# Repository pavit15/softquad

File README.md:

Soft Quad
===
## Table of Contents
- [About The Project](#about_the_project)
    - [Key elements of the project](#key_elements_of_the_project)
    - [Tech Stack](#tech_stack)
- [Getting Started](#getting_started)
    - [Prerequisites](#prerequisites)
    - [Installations](#installations)
- [Theory and Approach](#theory_and_approach) 
    - [Design of robot chassis](#design_of_robot_chasis)
    - [Selecting Flex Material for the bot](#selecting_material_for_the_bot)
- [Troit Gait Algorithm](#troit_gait_algorithm)
- [Challenges faced and solutions applied](#challenges_faced_and_solutions_applied)
- [Contributors](#contributors)
- [Acknowledgement and Resources](#acknowledgement_and_resources)
---

# <ins>About the Project
**To create a robot capable of overcoming obstacle using soft materials.**
Basically, in our project, we use flex material instead of rigid materials such as PLA. We used Ecoflex Dragon skin material for the body. A Flex PCB will enable our SoftQuad robot to become more flexible, improving its capacity to scale higher obstacles.
  
## <ins>Key elements of the project:
### 1. Mechanical design
The mechanical design and fabrication aspect of the project involve creating a design which is durable, flexible and lightweight to enable efficient movement. This design ensures both agility and robustness, allowing the robot to traverse challenging terrains while maintaining stability and precision.

### 2. Embedded design
In the core of the system, we use ESP32, a powerful microcontroller with built-in Wi-Fi and Bluetooth capabilities. It is programmed using the ESP-IDF (IoT Development Framework), which provides the tools and libraries necessary to develop applications for the microcontroller.

### 3. PCB design
The PCB (Printed Circuit Board) design involves creating a custom circuit board that has various electronic components such as microcontrollers, motor drivers, sensors, communication modules, and power management units. 

We used a Flex PCB, which is a type of electronic circuit board that is made from flexible and bendable materials instead of rigid materials like in traditional PCB’s. They offer a range of benefits due to their flexibility, allowing them to be shaped, folded, or bent to fit into various form factors and spaces that rigid PCBs cannot accommodate.
### 4. Soft robotics
Unlike traditional rigid robots, this project utilizes soft robotics principles to create a robot with a pliable and deformable structure. This inherent flexibility allows the robot to adapt its shape to various obstacles, enhancing its ability to traverse complex terrains.</ins>
</ins>

## <ins>Tech Stack
- Embedded C
- SolidWorks
- KiCAD
- Altium
- ESP-IDF
- Ultimaker Cura
    
# <ins>Getting Started
## <ins>Prerequisites
1. Used [ESP-IDFv4.4](https://docs.espressif.com/projects/esp-idf/en/latest/esp32/get-started) for building and flashing the controller code.
2. Used [KiCad](https://www.kicad.org/) For designing the rigid PCB
3. Used [Altium](https://www.altium.com/) For designing the flex PCB   
4. Used [Solidworks](https://www.solidworks.com/) for designing the bot and mold for soft bot.
5. Used [Ultimaker Cura](https://ultimaker.com/software/ultimaker-cura/) for 3D printing the parts

## <ins>Installations
1. Installing ESP-IDF:
[For Windows](https://docs.espressif.com/projects/esp-idf/en/latest/esp32/get-started/windows-setup.html)
[For Linux or MacOS](https://docs.espressif.com/projects/esp-idf/en/latest/esp32/get-started/linux-macos-setup.html)

# <ins>Theory and Approach
### Design of robot chasis
- We designed the chasis of the bot on Solidworks.

### Selecting Flex Material for the bot
- For the bot material, we had to choose between Dragon Skin, Eco-Flex 00-30, Eco-Flex 00-50
- After taking into account factors such as flexibility, durability, elasticity and stability, we concluded that Dragon Skin is the material most comparable to PDMS in terms of its flexibility, translucency, and biocompatibility. It is often used as a substitute when PDMS like properties are required, making it a versatile and obvious choice for applications such as soft robotics. 

## <ins>Trot Gait Algorithm
We controlled the movement of the bot through our ESP-32 controller. The motion that the bot follows is that of the horse trot gait. 
Here is a flowchart explaining the code: 

## <ins>PCB Design on KiCAD
Fornt side of PCB

Backside

## <ins>Challenges faced and solutions applied  
At first, the weight of the body was bending the flex legs since they were unable to support the weight of the bot. In order to allow the legs to move, we altered the leg's measurements and added thickness.Managing the soft robotics part is taking some time.
The main hardware and circuit problem we encountered was voltage control, or the inability to supply the appropriate and sufficient voltage to the corresponding electrical equipment.
We had to move to Altium because Kicad would not allow us to define stack layers, or create a flexible PCB with stiffeners. It took some getting used to.

## <ins>Making the flex body
For testing purposes, we made the rigid body of the bot using 3D printing first. After finishing with testing, we made the molds for the bot and 3D printed them. Then we made the mold of the bot using Dragon Skin material. For this process, initially we mixed the material  in 1:1 ratio for around 1 minute. Then we put this mixture in the mold and left it for around 2 hours.
    
DragonSkin material in the mold:

## <ins>Contributors
[Atharva Atre](https://github.com/AtharvaAtre)
[Pavit Kaur](https://github.com/pavit15)
[Varad Naik](https://github.com/VaradNaik921)
    
---

## <ins>Acknowledgement and Resources
Thanks to Our Mentors [Chinmay Mundane](https://github.com/ChinmayMundane), [Vaidic Gupta](https://github.com/Vaidicgupta) for Mentoring and Guiding us in our project.

Special Thanks to [SRA VJTI](https://sravjti.in/) for giving us the opportunity to do the project.

**Resources:**
- [**SoftBot Research Paper**](https://repository.bilkent.edu.tr/server/api/core/bitstreams/3dedb9bb-7897-4cc8-92b2-c85b78272922/content)
- [**ESP-IDF Resources**](https://docs.espressif.com/projects/esp-idf/en/latest/esp32/get-started/)
- [**KiCad Playlist**](https://www.youtube.com/playlist?list=PLn6004q9oeqGl91KifK6xHGuqvXGb374G)
- [**Solidworks Playlist**](https://www.youtube.com/playlist?list=PLrOFa8sDv6jcp8E3ayUFZ4iNI8uuPjXHe)

---

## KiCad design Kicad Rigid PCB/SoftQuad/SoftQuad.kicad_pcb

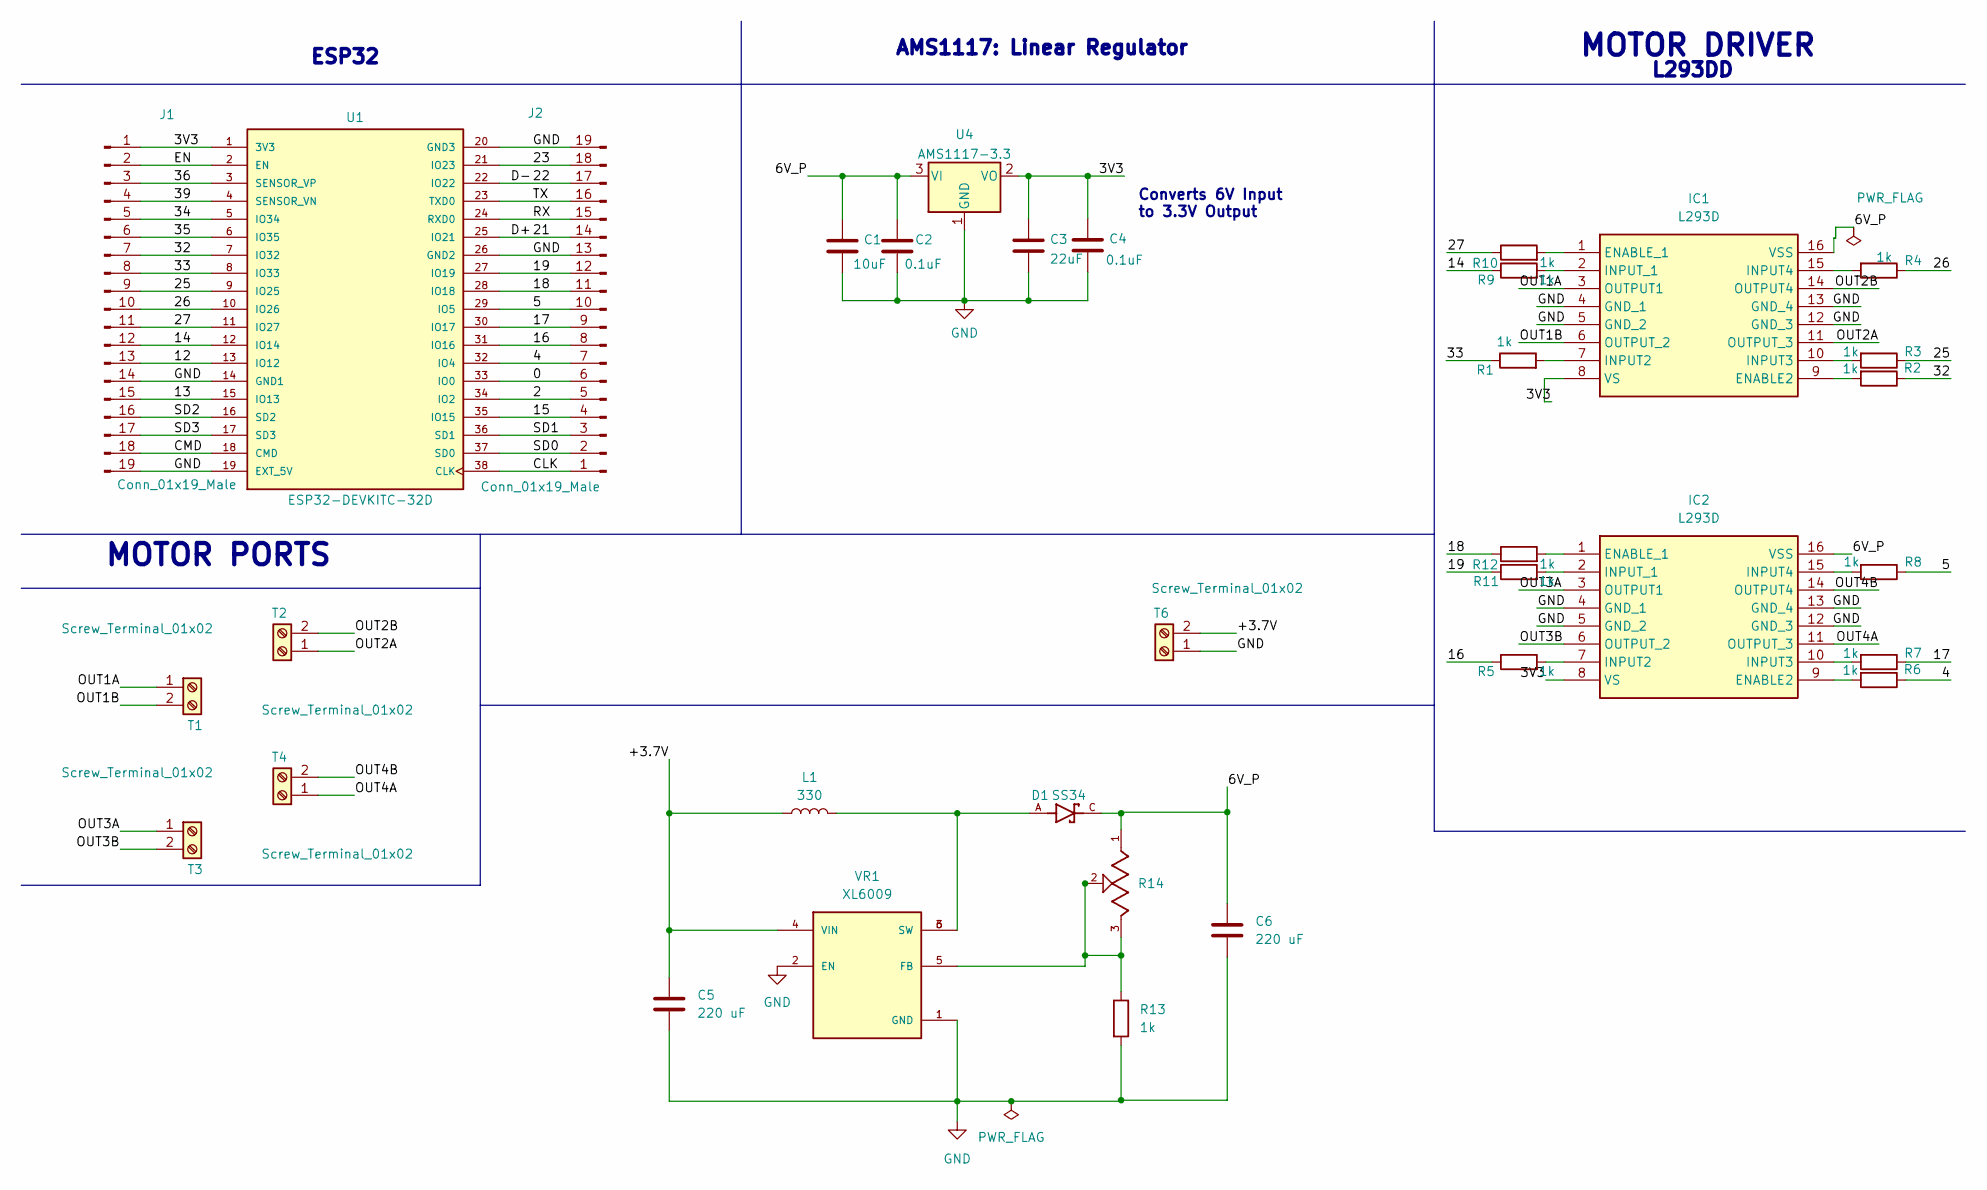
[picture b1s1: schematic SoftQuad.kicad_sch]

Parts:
C1: 10uF; C_0603_1608Metric
C2, C4: 0.1uF; C_0603_1608Metric
C3: 22uF; C_0603_1608Metric
C5, C6: 220 uF; C_0201_0603Metric
D1: SS34; DIOM7959X265N; PARTREV 31 Aug 2016
IC1, IC2: L293D; DIP880W50P254L2000H510Q16N; Manufacturer_Part_Number L293D; Mouser Part Number 511-L293D
J1, J2: Conn_01x19_Male; 1X19
L1: 330; L_0201_0603Metric
R1, R2, R3, R4, R5, R6, R7, R8, R9, R10, R11, R12, R13: 1k; R_0201_0603Metric
R14: 10k; TRIM_3352T-1-504LF; PARTREV 08/19
T1, T2, T3, T4, T6: Screw_Terminal_01x02; TerminalBlock_bornier-2_P5.08mm
U1: ESP32-DEVKITC-32D; ESP32-DEVKITCv4-32D; PARTREV 4
U4: AMS1117-3.3; SOT-223-3_TabPin2
VR1: XL6009; DPAK170P1435X465-6N; PARTREV 1.1

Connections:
/0: J2.6, U1.33 (IO0)
/2: J2.5, U1.34 (IO2)
/3V3: C3.1, C4.1, IC1.8 (VS), IC2.8 (VS), U1.1 (3V3), U4.2 (VO)
/4: R6.1, U1.32 (IO4)
/5: R8.1, U1.29 (IO5)
/6V_P: C1.1, C2.1, C6.1, D1.C, IC1.16 (VSS), IC2.16 (VSS), R14.1, U4.3 (VI)
/12: J1.13, U1.13 (IO12)
/13: J1.15, U1.15 (IO13)
/14: R9.1, U1.12 (IO14)
/15: J2.4, U1.35 (IO15)
/16: R5.1, U1.31 (IO16)
/17: R7.1, U1.30 (IO17)
/18: J2.11, R12.1, U1.28 (IO18)
/19: J2.12, R11.1, U1.27 (IO19)
/21: J2.14, U1.25 (IO21)
/22: J2.17, U1.22 (IO22)
/23: J2.18, U1.21 (IO23)
/25: R3.1, U1.9 (IO25)
/26: R4.1, U1.10 (IO26)
/27: R10.1, U1.11 (IO27)
/32: R2.1, U1.7 (IO32)
/33: R1.1, U1.8 (IO33)
/34: J1.5, U1.5 (IO34)
/35: J1.6, U1.6 (IO35)
/36: J1.3, U1.3 (SENSOR_VP)
/39: J1.4, U1.4 (SENSOR_VN)
/+3.7V: C5.1, L1.1, T6.2, VR1.4 (VIN)
/CLK: J2.1, U1.38 (CLK)
/CMD: J1.18, U1.18 (CMD)
/EN: J1.2, U1.2 (EN)
/OUT1A: IC1.3 (OUTPUT1), T1.1
/OUT1B: IC1.6 (OUTPUT_2), T1.2
/OUT2A: IC1.11 (OUTPUT_3), T2.1
/OUT2B: IC1.14 (OUTPUT4), T2.2
/OUT3A: IC2.3 (OUTPUT1), T3.1
/OUT3B: IC2.6 (OUTPUT_2), T3.2
/OUT4A: IC2.11 (OUTPUT_3), T4.1
/OUT4B: IC2.14 (OUTPUT4), T4.2
/RX: J2.15, U1.24 (RXD0)
/SD0: J2.2, U1.37 (SD0)
/SD1: J2.3, U1.36 (SD1)
/SD2: J1.16, U1.16 (SD2)
/SD3: J1.17, U1.17 (SD3)
/TX: J2.16, U1.23 (TXD0)
GND: C1.2, C2.2, C3.2, C4.2, C5.2, C6.2, IC1.4 (GND_1), IC1.5 (GND_2), IC1.12 (GND_3), IC1.13 (GND_4), IC2.4 (GND_1), IC2.5 (GND_2), IC2.12 (GND_3), IC2.13 (GND_4), R13.2, T6.1, U1.14 (GND1), U1.19 (EXT_5V), U1.20 (GND3), U1.26 (GND2), U4.1 (GND), VR1.1 (GND), VR1.2 (EN)
unnamed: D1.A, L1.2, VR1.3 (SW), VR1.6 (SW)
unnamed: IC1.9 (ENABLE2), R2.2
unnamed: IC1.1 (ENABLE_1), R10.2
unnamed: IC1.7 (INPUT2), R1.2
unnamed: IC1.10 (INPUT3), R3.2
unnamed: IC1.15 (INPUT4), R4.2
unnamed: IC1.2 (INPUT_1), R9.2
unnamed: IC2.9 (ENABLE2), R6.2
unnamed: IC2.1 (ENABLE_1), R12.2
unnamed: IC2.7 (INPUT2), R5.2
unnamed: IC2.10 (INPUT3), R7.2
unnamed: IC2.15 (INPUT4), R8.2
unnamed: IC2.2 (INPUT_1), R11.2
unnamed: R13.1, R14.2, R14.3, VR1.5 (FB)

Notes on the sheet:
L293DD
Converts 6V Input to 3.3V Output
MOTOR DRIVER
MOTOR PORTS
ESP32
AMS1117: Linear Regulator

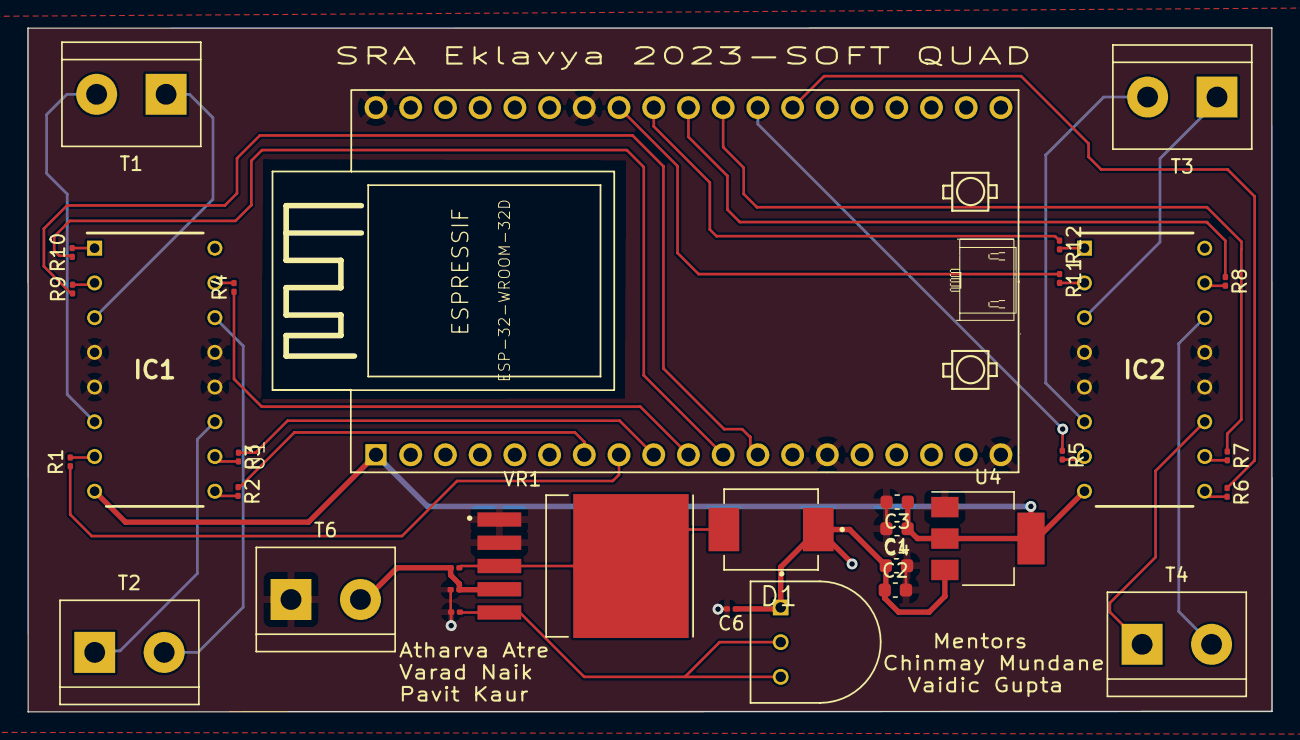
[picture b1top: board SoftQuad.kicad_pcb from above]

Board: 2 copper layers, 91.0 x 50.0 mm, 32 parts (0 on the bottom side), 38 nets.

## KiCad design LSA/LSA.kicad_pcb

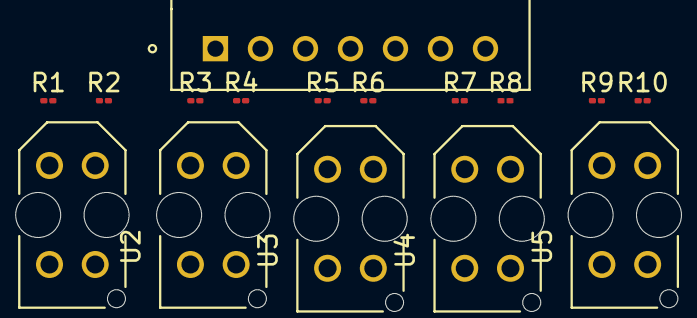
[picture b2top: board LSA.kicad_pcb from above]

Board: 2 copper layers, 16 parts (0 on the bottom side), 12 nets, no tracks yet.

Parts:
P1: S7B-XH-A(LF)(SN); JST_S7B-XH-A(LF)(SN)
R1, R3, R5, R7, R9: 4.7K; R_01005_0402Metric
R2, R4, R6, R8, R10: 150R; R_01005_0402Metric
U1, U2, U3, U4, U5: TCRT5000; OPTO_TCRT5000

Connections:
/3V3: P1.7, R1.1, R2.2, R3.1, R4.2, R5.1, R6.2, R7.1, R8.2, R9.1, R10.2
/A0-36: P1.1, R1.2, U1.COLL
/A1-39: P1.2, R3.2, U2.COLL
/A2-34: P1.3, R5.2, U3.COLL
/A3-35: P1.4, R7.2, U4.COLL
/A4-32: P1.5, R9.2, U5.COLL
/GND: P1.6, U1.CATH, U1.E, U2.CATH, U2.E, U3.CATH, U3.E, U4.CATH, U4.E, U5.CATH, U5.E
unnamed: R2.1, U1.A
unnamed: R4.1, U2.A
unnamed: R6.1, U3.A
unnamed: R8.1, U4.A
unnamed: R10.1, U5.A

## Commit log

2023-08-18 Create ESP 32 Pins, Normal and parallel mode in ESP32
2023-08-18 Create Code LED Flash and Hello World
2023-08-19 last changed at Aug 19, 2023 11:40 PM, pushed by pavit
2023-08-19 ESP-IDF Flash Commands
2023-08-19 README.md
2023-08-20 ESP IDF Commands.md
2023-08-20 LED Blink.md
2023-08-24 SoftQuad.md
2023-08-24 Create a
2023-08-24 ESP32.md
2023-08-24 PWM.md
2023-09-23 Create Solidwork Parts
2023-11-04 Create aa
2023-11-04 Components used for solidworks assembly
2023-11-04 Solidworks Rigid Bot Parts
2023-11-04 Rigid Bot Designs
    Final Design used for 3D printing and making of Rigid Bot
2023-11-04 Mold Designs
    Molds used for Making the flexible parts
2023-11-04 Molds Solidworks
    Mold Designs used for making flexible chassis and legs
2023-11-04 STL Files for 3D Printing
    STL files used for 3D printing the mold and parts of rigid bot
2023-11-04 STL Files used in 3D printing
    STL files used for 3D printing the parts of rigid bot and mold used in making soft bot
2023-11-04 Prototype cad model
2023-11-04 Prototype CAD Models
2023-11-04 assets for cad_design
2023-11-04 Assembly Files
    Assembly created for bot
2023-11-04 Adding Report
2023-11-05 assets
2023-11-05 Prototype PCB design for 6V battery
2023-11-05 Final Flex PCB design for a 3.7V Battery
2023-11-05 LSA PCB Design(Practice)
2023-11-05 components used in assembly
2023-11-05 Models of Rigid Bot
2023-11-05 Rigid Bot Models
2023-11-05 Molds for Soft Bot Fabrication
2023-11-05 STL Files used for 3D printing
2023-11-05 STL Files for 3D Printing
2023-11-05 Assembly of Bot in Solidworks
2023-11-05 Assembly of Bot
2023-11-05 Rigid PCB(KICAD)
2023-11-05 CAD_Design used in Project
2023-11-05 Create Re
2023-11-05 CAD_Designs used in project
2023-11-05 CAD Designs used in Project
2023-11-05 CAD Design used in Project
2023-11-05 CAD Designs
2023-11-05 CAD prototype
2023-11-05 Report Update
2023-11-05 KiCAD files
2023-11-05 Prototype Models
2023-11-05 CAD_Designs
